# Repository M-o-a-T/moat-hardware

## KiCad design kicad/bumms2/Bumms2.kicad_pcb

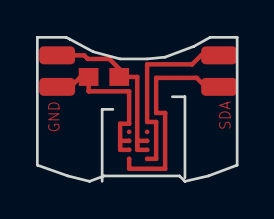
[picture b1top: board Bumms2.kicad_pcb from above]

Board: 2 copper layers, 11.1 x 8.0 mm, 6 parts (0 on the bottom side), 4 nets.

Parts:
C1: 220nF; C0603
JP1, JP2, JP3, JP4: PINHD-1X1PAD; 1PAD
U$1: HDC1008; BGA8_HDC

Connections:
unnamed: C1.1, JP1.P$1, U$1.B1, U$1.C1
unnamed: C1.2, JP2.P$1, U$1.B2, U$1.C2
unnamed: JP3.P$1, U$1.A2
unnamed: JP4.P$1, U$1.A1

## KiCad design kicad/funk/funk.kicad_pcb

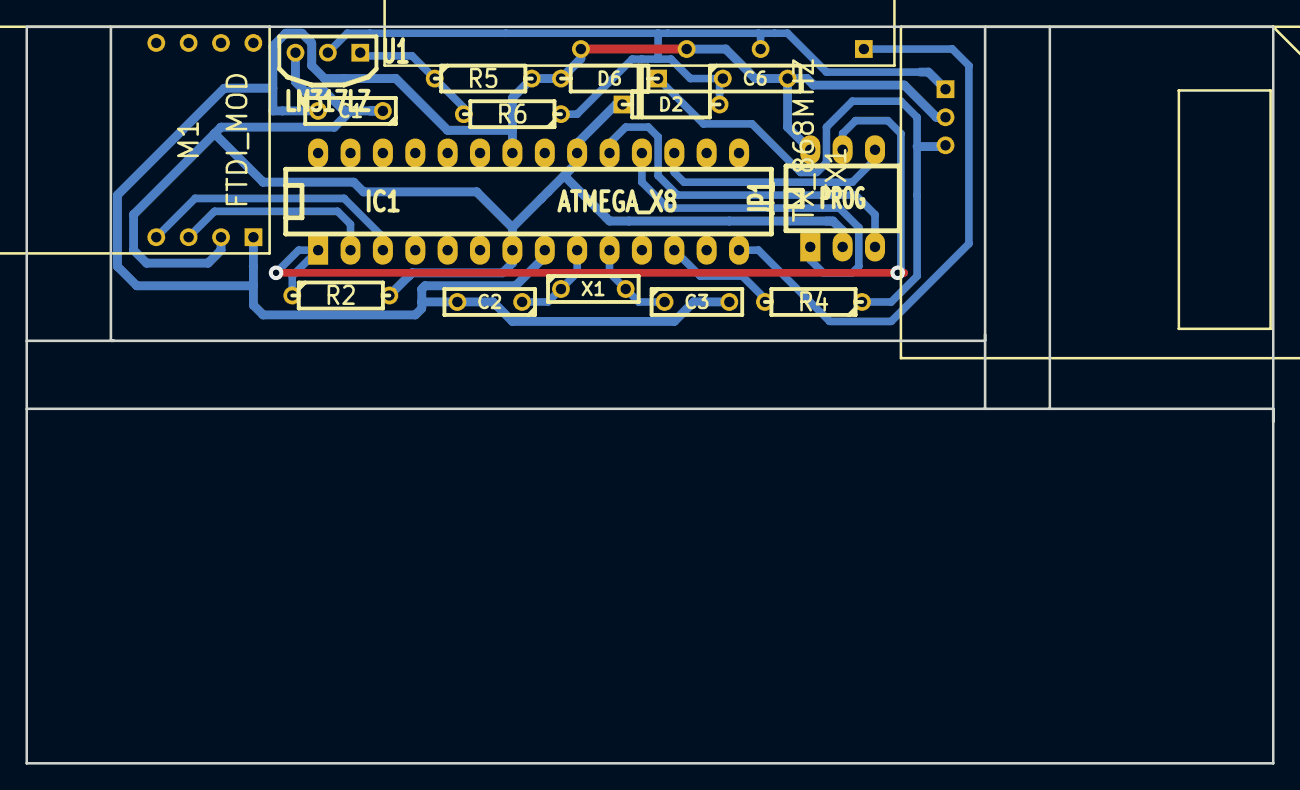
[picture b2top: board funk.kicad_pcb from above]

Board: 2 copper layers, 97.8 x 57.8 mm, 17 parts (0 on the bottom side), 15 nets.

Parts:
C1: 100n; C2
C2, C3: 10p; C2
C6: 1u; C2
D2: 1N4001; D3
D6: 2.7; D3
IC1: ATMEGA_X8; 28DIP-ELL300
JP1: PROG; 6DIP-ELL300
M1: FTDI_MOD; FTDI
R2: 10k; R3
R4: 1k; R3
R5: 160; R3
R6: 220; R3
RX1: RX_868MHZ; Rx_868
TX1: TX_868MHZ; Tx_686
U1: LM317LZ; TO92_inline
X1: 16_MHz; C2

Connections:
+3.3V: C6.1, D2.1, R6.1, RX1.2, TX1.1, U1.2
+5V: C1.1, D2.2, IC1.7, IC1.20, JP1.2, M1.2, R2.2, U1.3
GND: C1.2, C2.2, C3.2, C6.2, D6.1, IC1.8, IC1.22, JP1.6, M1.1, R5.2, RX1.3, RX1.4, TX1.2
unnamed: IC1.12, R4.2
unnamed: IC1.2, M1.3
unnamed: IC1.3, M1.4
unnamed: IC1.19, JP1.3
unnamed: IC1.1, JP1.5, R2.1
unnamed: IC1.14, RX1.1
unnamed: IC1.18, JP1.1
unnamed: IC1.17, JP1.4
unnamed: D6.2, R4.1, TX1.3
unnamed: R5.1, R6.2, U1.1
unnamed: C3.1, IC1.10, X1.2
unnamed: C2.1, IC1.9, X1.1

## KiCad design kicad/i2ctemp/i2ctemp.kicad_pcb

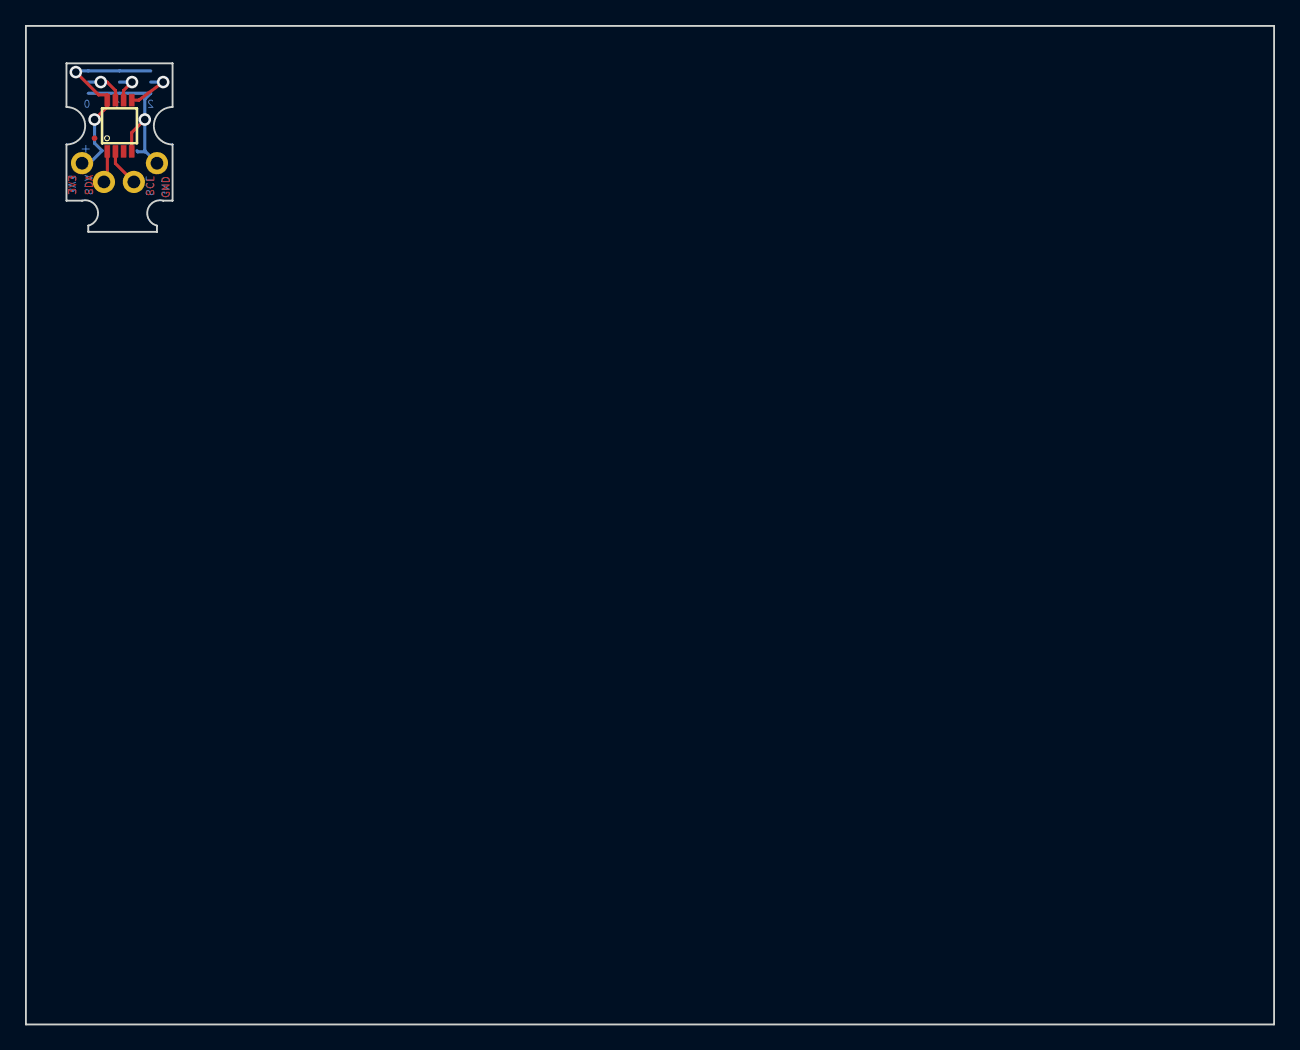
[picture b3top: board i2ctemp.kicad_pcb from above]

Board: 2 copper layers, 100.0 x 80.0 mm, 9 parts (0 on the bottom side), 7 nets.

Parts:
3V3: PINHD-1X1CB; 1X01-CLEANBIG
AJ0, AJ1, AJ2: SJ3S; SJ3_S
C1: CP1206
GND1: PINHD-1X1CB; 1X01-CLEANBIG
SCK1: PINHD-1X1CB; 1X01-CLEANBIG
SDA1: PINHD-1X1CB; 1X01-CLEANBIG
TEMP1: MCP9808MSOP; MSOP8

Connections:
unnamed: 3V3.1, AJ0.2, AJ1.2, AJ2.2, C1.+, TEMP1.8
unnamed: AJ0.1, AJ1.1, AJ2.1, C1.-, GND1.1, TEMP1.4
unnamed: AJ0.COM, TEMP1.7
unnamed: AJ1.COM, TEMP1.6
unnamed: AJ2.COM, TEMP1.5
unnamed: SCK1.1, TEMP1.2
unnamed: SDA1.1, TEMP1.1

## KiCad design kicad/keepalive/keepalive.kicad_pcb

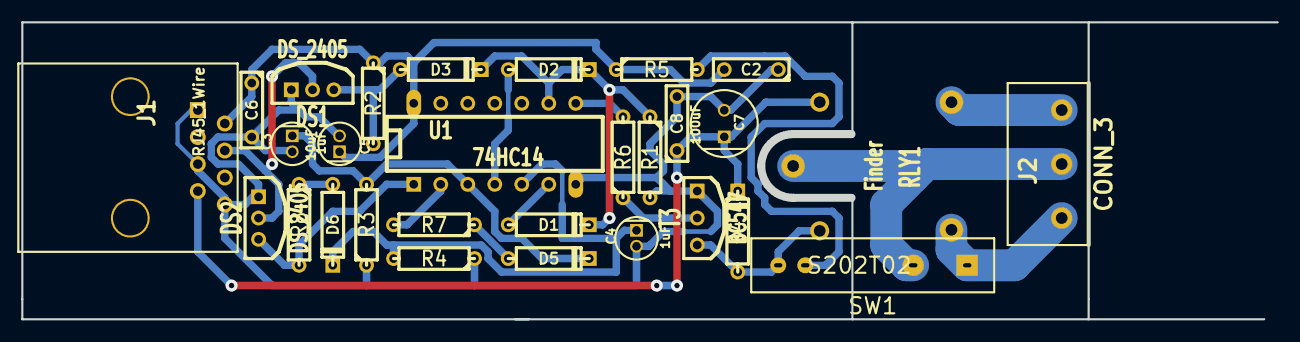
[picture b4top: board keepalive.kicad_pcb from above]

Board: 2 copper layers, 118.1 x 27.9 mm, 29 parts (0 on the bottom side), 21 nets.

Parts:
C2, C6: 10nF; C2
C3, C4: 1uF; Elko_1.5
C5: 10uF; Elko_1.5
C7: 100uF; Elko_2.5
C8: 100nF; C2
D1, D2, D3, D4, D5, D6: 1N4148; D3
DS1, DS2: DS_2405; TO92_inline_2mm
J1: RJ45_1Wire; RJ45_8_R
J2: CONN_3; 3pin_r2
R1: 1M; R3
R2: 22K; R3
R3, R4: 10M; R3
R5: 180; R3
R6: 10k; R3
R7, R8: 1k; R3
RLY1: Finder; Finder_36.11.9.012
SW1: S202T02
T3: BC547; TO92_inline
U1: 74HC14; 14dip300

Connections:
+5V: C2.2, C5.1, C6.1, J1.2, R2.1, R5.1, U1.14
+12V: C7.1, C8.1, D4.2, J1.7, RLY1.1
GND: C2.1, C3.2, C4.2, C5.2, C6.2, C7.2, C8.2, DS1.1, DS2.1, J1.1, J1.5, J1.8, R1.2, R3.1, R4.1, T3.1, U1.7
unnamed: J2.2, RLY1.3, SW1.2
unnamed: R6.2, U1.8
unnamed: R7.2, U1.2
unnamed: D6.1, R8.1
unnamed: D1.1, U1.6
unnamed: R5.2, SW1.3
unnamed: DS1.2, DS2.2, J1.4
unnamed: D3.1, DS1.3, R2.2
unnamed: J2.1, RLY1.4
unnamed: D1.2, D2.2, D3.2, R1.1, U1.9
unnamed: D2.1, U1.4
unnamed: D5.1, R7.1
unnamed: R6.1, T3.2
unnamed: J2.3, RLY1.5, SW1.1
unnamed: DS2.3, R8.2, U1.1
unnamed: D4.1, RLY1.2, SW1.4, T3.3
unnamed: C4.1, D6.2, R4.2, U1.5
unnamed: C3.1, D5.2, R3.2, U1.3

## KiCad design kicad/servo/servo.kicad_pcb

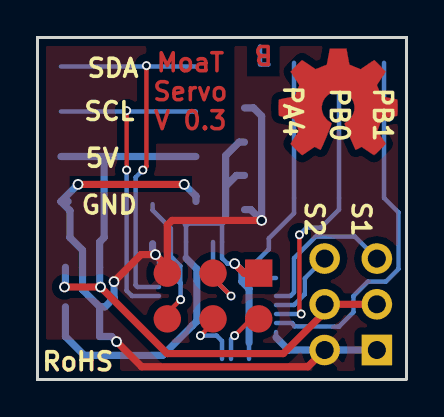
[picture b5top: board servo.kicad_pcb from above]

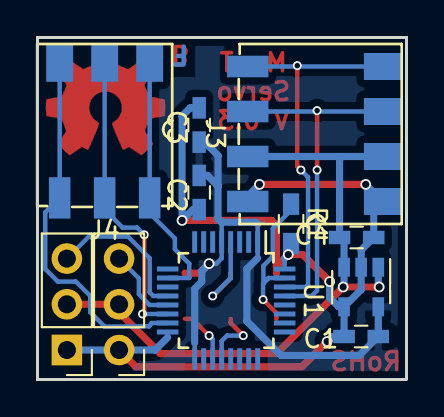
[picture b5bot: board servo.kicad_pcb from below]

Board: 2 copper layers, 20.5 x 19.0 mm, 12 parts (11 on the bottom side), 14 nets.

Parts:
C1, C4: 1µF; C_0603_HandSoldering
C2: 10nF; C_0603_HandSoldering
C3: 100nF; C_0603_HandSoldering
J1: Servo 1; Pin_Header_Straight_1x03_Pitch2.54mm
J2: Servo 2; Pin_Header_Straight_1x03_Pitch2.54mm
J3: System; AVX_9276_4Pin_HS
J4: I/O; AVX_9276_3Pin_HS
Prog1: PogoPad; PogoPad_2x3_SMD
R1: 10k; R_0603_HandSoldering
U1: STM32F030K6Tx; LQFP-32_5x5mm_Pitch0.5mm
U2: TPS76333; SOT-23-5

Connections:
+3V3: C1.1, C2.1, C3.1, Prog1.1, U1.1, U1.5, U1.17, U2.5
+5V: C4.1, J1.2, J2.2, J3.2, U2.1, U2.3
/Rx: Prog1.4, U1.20
/SCL: J3.3, U1.29
/SDA: J3.4, U1.30
/Servo1: J1.3, U1.12
/Servo2: J2.3, U1.13
/Tx: Prog1.2, U1.19
GND: C1.2, C2.2, C3.2, C4.2, J1.1, J2.1, J3.1, Prog1.5, R1.2, U1.16, U1.32, U2.2, U2.4
unnamed: J4.1, U1.10
unnamed: J4.2, U1.14
unnamed: J4.3, U1.15
unnamed: Prog1.3, U1.4
unnamed: Prog1.6, R1.1, U1.31

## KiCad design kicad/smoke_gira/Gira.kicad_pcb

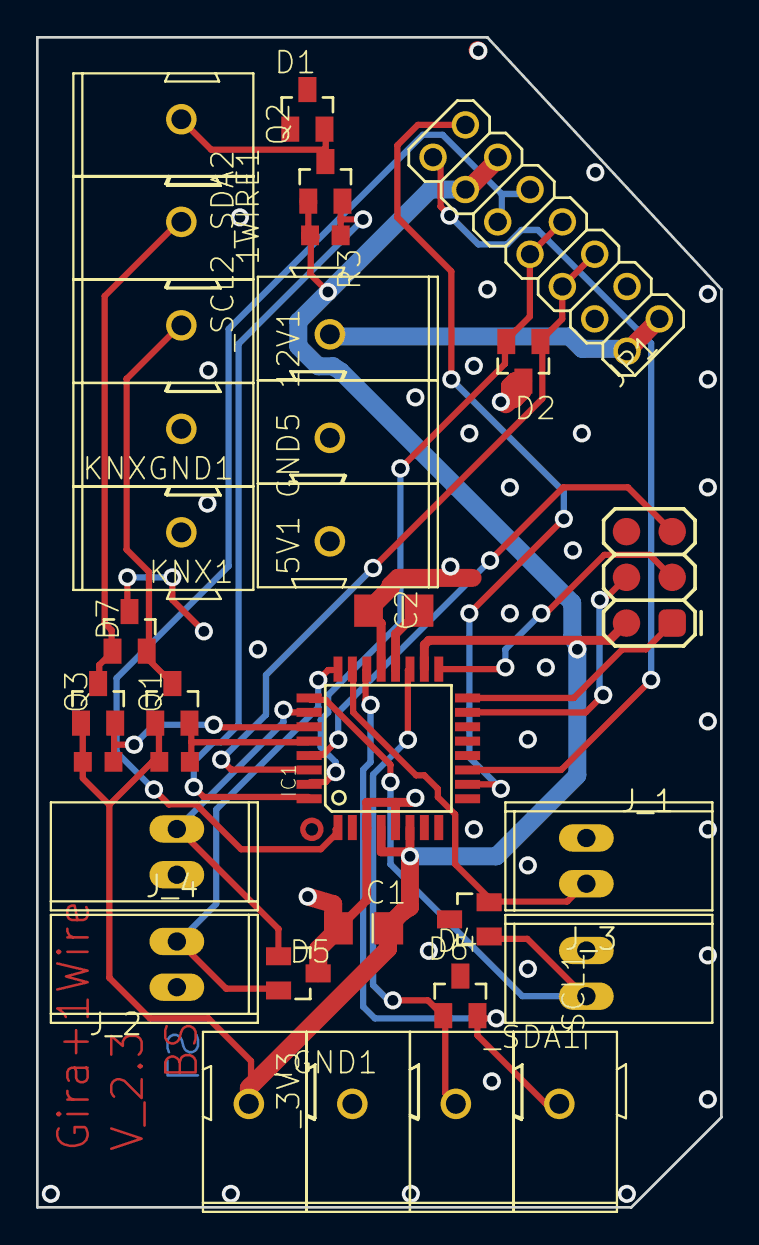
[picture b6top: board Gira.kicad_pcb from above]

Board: 2 copper layers, 38.0 x 65.0 mm, 33 parts (0 on the bottom side), 22 nets.

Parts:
1WIRE1, 5V1, 12V1: WAGO_243
C1, C2: CP1206
D1, D2, D4, D5, D6, D7: ESD_DIODES; SOT23
GND5: WAGO_243
IC1: MEGA8-PTQFP; TQFP32-08
JP1: PINHD-2X7; 2X07
J_1, J_2, J_3, J_4: PINHD-1X2LEVER; 1X02_GN
KNX1: WAGO_243
KNXGND1: WAGO_243
Q1, Q2, Q3: 2N7002; SOT23
R1, R2, R3: R-EU_R0603; R0603
U$1: AVR_SPI_PRG_6PAD; 2X3_PAD
_3V3: WAGO_243
_GND1: WAGO_243
_SCL1, _SCL2: WAGO_243
_SDA1, _SDA2: WAGO_243

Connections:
+3V3: C1.+, D6.1, D6.2, IC1.4, IC1.6, IC1.18, IC1.19, IC1.22, JP1.11, JP1.12, Q1.1, Q2.1, Q3.1, R1.2, R2.2, R3.2, U$1.P$2, _3V3.P$1, _SCL1.P$1, _SDA1.P$1
/B1: D4.2, IC1.23, J_1.2
/B2: D5.2, IC1.10, IC1.24, J_2.2
/B3: D4.1, IC1.25, J_3.2
/B4: D5.1, IC1.26, J_4.2
/SCL2: IC1.28, Q1.2, R2.1
/SDA2: IC1.27, Q3.2, R1.1
/TEST: IC1.11, JP1.14
GND: C1.-, C2.-, D1.3, D2.3, D4.3, D5.3, D6.3, D7.3, GND5.P$1, IC1.3, IC1.5, IC1.21, JP1.3, JP1.4, J_1.1, J_2.1, J_3.1, J_4.1, U$1.P$6, _GND1.P$1
unnamed: 1WIRE1.P$1, D1.2, Q2.3
unnamed: 12V1.P$1, JP1.1, JP1.2
unnamed: C2.+, IC1.20
unnamed: D2.1, IC1.30, JP1.5, JP1.6
unnamed: D2.2, IC1.31, JP1.7, JP1.8
unnamed: D7.1, Q3.3, _SDA2.P$1
unnamed: D7.2, Q1.3, _SCL2.P$1
unnamed: IC1.1, JP1.9, JP1.10
unnamed: IC1.15, U$1.P$4
unnamed: IC1.16, U$1.P$1
unnamed: IC1.17, U$1.P$3
unnamed: IC1.29, U$1.P$5
unnamed: IC1.32, Q2.2, R3.1

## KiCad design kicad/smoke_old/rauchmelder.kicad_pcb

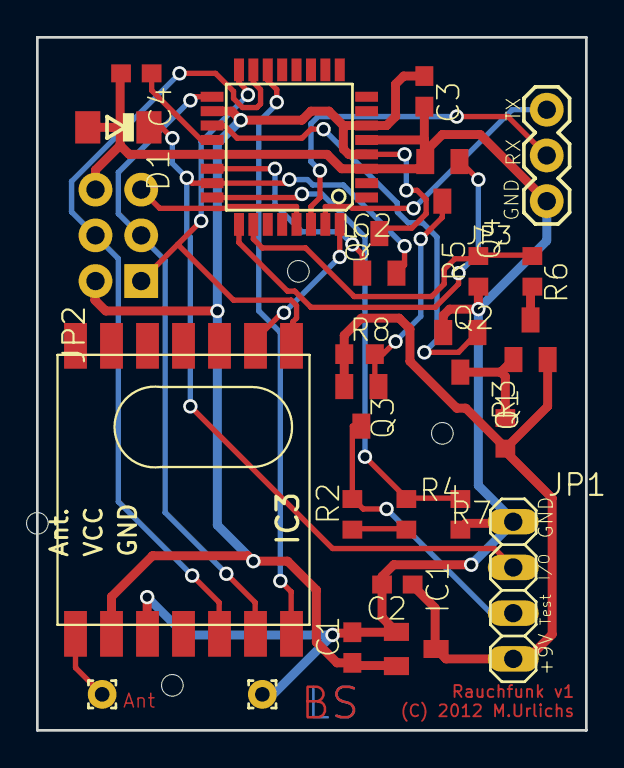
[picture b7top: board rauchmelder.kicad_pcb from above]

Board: 2 copper layers, 30.5 x 38.5 mm, 32 parts (0 on the bottom side), 24 nets.

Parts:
@HOLE0, @HOLE1, @HOLE2, @HOLE3: (no value)
C1, C2: 1u; C0603
C3, C4: 100n; C0603
D1: 3V; SOD80C
IC1: MCP1703CB; SOT23
IC2: MEGA8-MITQFP; TQFP32-08
IC3: RFM12B
JP1: RM; 1X04
JP2: AVR_SPI_PRG_6NS; 2X3-NS
JP3: ser; 1X03
PAD1: Ant; 1,6_0,8
PAD2: 1,6_0,8
Q1, Q4, Q5: 2N7002_SMD; SOT23
Q2, Q3: NX3008; SOT23
R2, R3, R4, R6, R7, R8: 100k; R0603
R5: 10k; R0603
U$1, U$2, U$3: FIDUCIAL

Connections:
+5V: C1.1, C3.1, IC1.2, IC2.4, IC2.6, IC2.18, IC3.VDD, JP2.2, Q5.3
/BATTERY: C2.1, IC1.3, JP1.4, Q2.2, Q3.2, R3.2, R8.1
/BAT_IN: IC2.26, R5.2, R6.1
/BAT_OUT: IC2.19, Q1.1
/IO_IN: D1.C, IC2.23, JP1.2, Q5.2
/IO_OUT: IC2.22, Q5.1
/TEST: JP1.3, Q3.3, R2.2
/TEST_IN: IC2.24, R4.1, R7.2
/TEST_OUT: IC2.25, Q4.1
GND: C1.2, C2.2, C3.2, C4.2, D1.A, IC1.1, IC2.3, IC2.5, IC2.21, IC3.GND, JP1.1, JP2.6, JP3.1, PAD2.1, Q1.2, Q4.2, R5.1, R7.1
unnamed: C4.1, IC2.20
unnamed: IC2.14, IC3.SEL
unnamed: IC2.15, IC3.SDI, JP2.4
unnamed: IC2.16, IC3.SDO, JP2.1
unnamed: IC2.17, IC3.SCK, JP2.3
unnamed: IC2.29, JP2.5
unnamed: IC2.30, JP3.2
unnamed: IC2.31, JP3.3
unnamed: IC2.32, IC3.IRQ
unnamed: IC3.ANT, PAD1.1
unnamed: Q1.3, Q2.1, R3.1
unnamed: Q2.3, R6.2
unnamed: Q3.1, Q4.3, R8.2
unnamed: R2.1, R4.2

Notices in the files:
kicad/smoke_old/rauchmelder.kicad_pcb:
(C) 2012 M.Urlichs
